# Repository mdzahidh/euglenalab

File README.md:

# Build Instruction
After cloning you need to do the following extra steps:
* git submodule init
* git submodule update --recursive
* cd into the bpu/ImageStreamer and run "make"
* cd into processing and run "build.sh"

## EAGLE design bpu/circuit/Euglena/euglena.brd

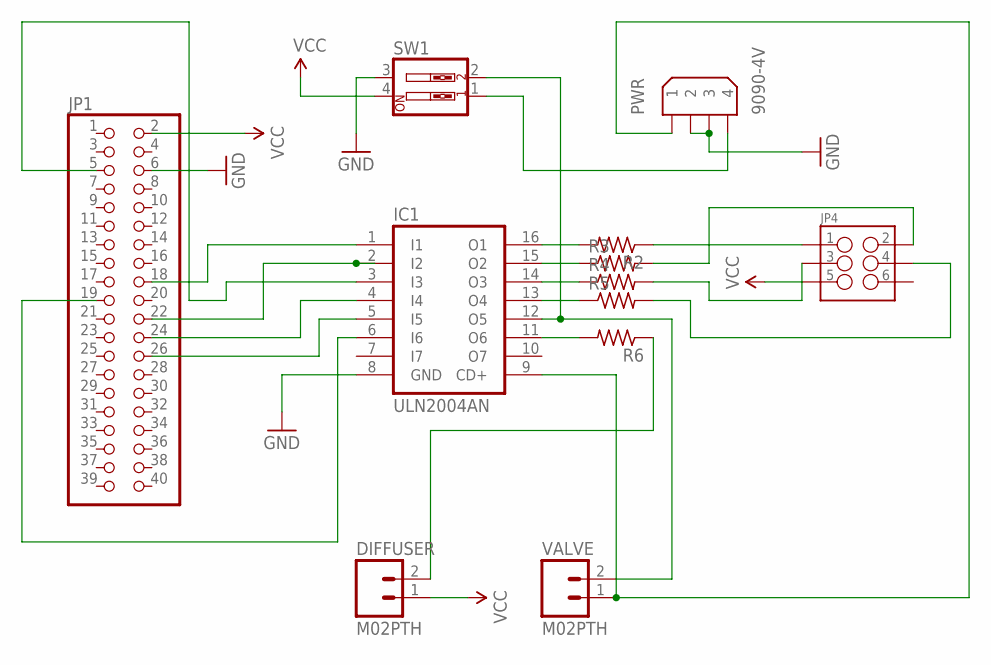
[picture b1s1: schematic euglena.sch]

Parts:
DIFFUSER: M02PTH; 1X02
IC1: ULN2004AN; DIL16
JP1: PINHD-2X20; 2X20
JP4: M03X2NO_SILK; 2X3-NS
PWR: 9090-4V
R2, R3, R4, R5, R6: R-US_0204/5; 0204/5
SW1: SW_DIP-2; DIPSWITCH-02
VALVE: M02PTH; 1X02

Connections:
5V: PWR.4, SW1.1
12V: IC1.9 (CD+), PWR.1, VALVE.1
GND: IC1.8 (GND), JP1.6, PWR.2, PWR.3, SW1.3
unnamed: IC1.16 (O1), R2.2
unnamed: IC1.2 (I2), JP1.22
unnamed: IC1.15 (O2), R3.1
unnamed: IC1.14 (O3), R4.1
unnamed: IC1.13 (O4), R5.1
unnamed: JP4.4, R5.2
unnamed: JP4.1, R2.1
unnamed: JP4.2, R3.2
unnamed: JP4.3, R4.2
unnamed: IC1.11 (O6), R6.2
unnamed: IC1.4 (I4), JP1.24
unnamed: IC1.1 (I1), JP1.18
unnamed: IC1.5 (I5), JP1.26
unnamed: IC1.3 (I3), JP1.5
unnamed: DIFFUSER.2, R6.1
unnamed: IC1.12 (O5), SW1.2, VALVE.2
unnamed: IC1.6 (I6), JP1.19
VCC: DIFFUSER.1, JP1.2, JP4.5, SW1.4

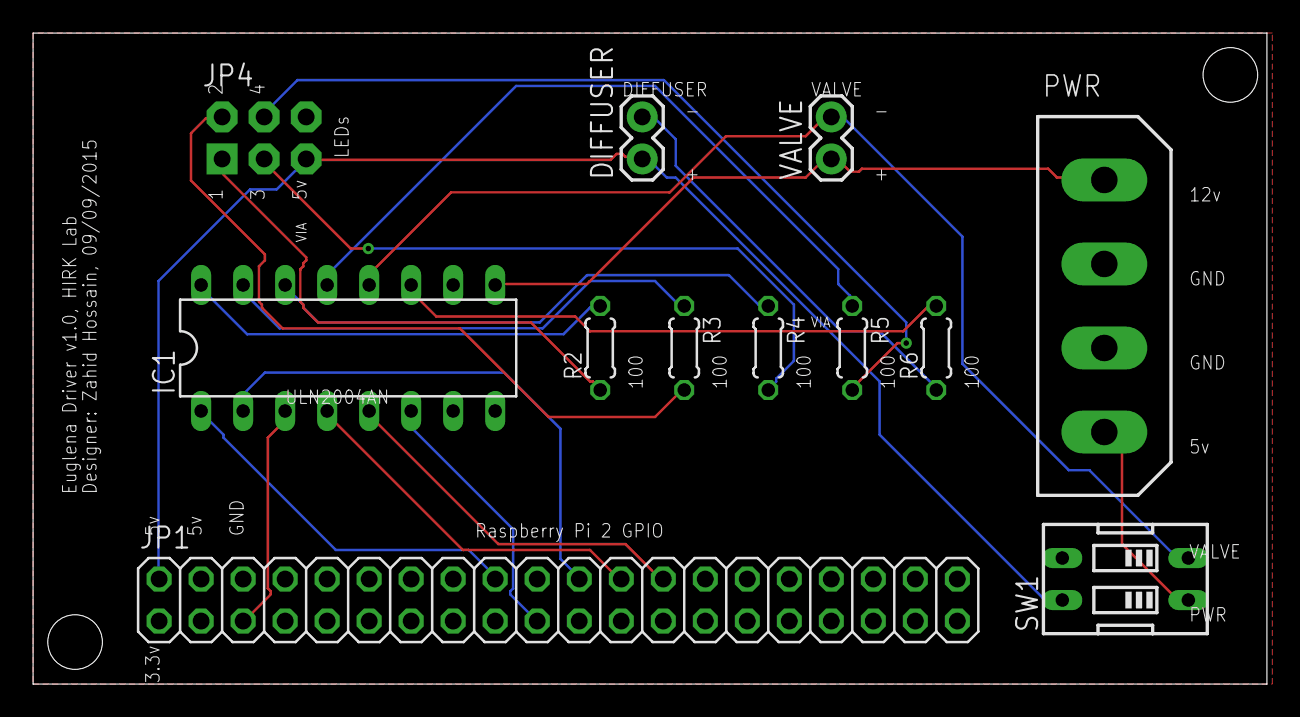
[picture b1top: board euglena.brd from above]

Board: 2 copper layers, 74.6 x 39.4 mm, 14 parts (0 on the bottom side), 21 nets.

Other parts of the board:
E$1, E$2: STAND-OFF

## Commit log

2016-06-07 added script to add all the BPUs in the databse
2016-06-07 package.json updated inside the bpu
2016-06-07 added the correct raspicam module
2016-06-07 git modules updated
2016-06-08 full system working without the external cam for now
2016-06-08 adding routing iptable settings for the debugging server
2016-06-08 adding routing table for accessing public ip from inside the the LAN
2016-06-08 fixed the bug related to multiple activateLiveUser issue when bpuController is restarted
2016-06-08 fixed a bug in the iptables routing
2016-06-09 refactored the configuration system
2016-06-09 deployment script missing
2016-06-09 fixed the bug related to user gettting stuck forever in a BPU when it crashes in the middle of an experiment
2016-06-09 fixed bug related to BPU failing for whatever other reason and user again getting stuck
2016-06-10 added excel sheet creator
2016-06-10 adding the Euglena Module
2016-06-10 modified the format
2016-06-10 had forgotten to multiply with the correct length scale
2016-06-15 adding the raspicam for the commit 5f6adee
2016-06-15 updating the euglenatracer
2016-06-15 adding the build script
2016-06-15 not mounting BPU directory automatically anymore
2016-06-15 added support for production/development export an environment variable GRUNT_ENV=production, otherwise its development, and also fixed a bug in teh time calculation when you upload a text file
2016-06-15 fixed problems in the gruntfile
2016-06-15 fixed the raspicam submodule for a specific commit 5f6adee and added separate scripts for setting up the servers vs bpus
2016-06-16 added the led setup in the BPU setup script
2016-06-20 updating Excel generation
2016-06-20 updated all Excel generation codes
2016-06-22 updats
2016-06-25 adding font file copy command in gruntfile for the glyphicons to work
2016-06-26 changed the basic captions and redirect to the main page after creating account
2016-06-27 updated labels
2016-06-27 fixed the relative scale size problem
2016-06-27 updated the submodule verison of euglentracer
2016-06-27 bug in controller and removing play button from the details.jade
2016-06-27 updated the euglenatracer
2016-06-27 updated the euglenatracer code
2016-06-27 added about and removed junks
2016-06-27 homepage updated
2016-06-27 Account page updated
2016-06-27 BPU changed to microscope
2016-07-01 added ingmars latest excel
2016-07-01 fixed a bug in the getNumFrame
2016-07-02 changed the header format
2016-07-18 euglentracer updated
2016-07-18 updated just before deployment
2016-07-26 debugged the paging issue:
2016-07-26 added the deployment.sample file back
2016-07-26 added google analytics
2016-08-10 adding the response script new version
2016-08-10 response script operates on gray scale now
2016-08-10 histogram equalization added
2016-11-02 Modelling platform api
2016-11-07 direct api for bps controller
2016-11-08 dev specific changes
2016-11-09 update auth info
2016-11-12 deploy
2016-11-12 single file download
2016-11-12 download
2016-11-12 file issue
2016-11-12 fix path
2016-11-23 fix experiment list bug
2016-11-23 fixing bug: can't send headers
2016-11-29 update path and add cars
2016-12-03 experiment status
2016-12-03 experiment status api
2016-12-03 status messages for client
2016-12-06 clean
2017-01-05 added the led init into the startup script
2017-01-11 Build instruction
2017-01-14 removing serialport dependancy from the bpu
2017-01-18 updates, a mysterious bug is still there that causes experiments from listexperiments.newExps to move over to the queues, which causes serious blockage
2017-01-24 automatic exposure turned off in the script now
2017-01-24 added a script for running bpu with image streamer inside a screen session from the root folder
2017-01-31 adding all the run scripts
2017-01-31 adding zip file support instead of old tar.gz
2017-02-02 added the first golang processing script
2017-02-03 reading database properly, but the naming convention is still confusing
2017-02-06 new processing server seems to be working well
2017-02-06 reduced the number of workers to 4. Each worker actually uses up all the cores due to internal tools
2017-02-07 changed all the run scripts to avoid automatic logging
2017-02-07 running it on the production server, so far no problems found, we keep this running
2017-02-07 setting it to point to the master branch of euglenatracer
2017-02-08 build script modified to install on a clean machine better
2017-02-08 added libav-tool in the install list
2017-02-08 adding xlsxwriter
2017-02-15 status messages done better
2017-02-15 modified slightly for the production server
2017-02-16 added logger for only errors
2017-02-16 timing information also displayed
2017-02-22 added seperate build script for installing opencv 3.1.0 python module
2017-03-01 Added Tahrina's new leds file
2017-03-08 Add missing packages, iptables script, .gitignore
2017-03-09 Decimal to Hex conversion capability added
2017-03-09 Fixing conversion method and supporting floating input
2017-03-14 updating euglentracer submodule
2017-03-14 updating euglentracer in the production

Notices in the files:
parts and their libraries:
SparkFun-Connectors: Licensing: CC v3.0 Share-Alike You are welcome to use this library for commercial purposes.
